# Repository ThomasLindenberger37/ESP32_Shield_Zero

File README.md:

# ESPhome Shield Zero

This project is a compact ESPhome compatible multisensor shield. The PCB is designed so that all required components can be hand-soldered—no SMD reflow oven or pick-and-place machine is required.
We want to eather use SMD componets that can be solderd by hand with a soldering iron or we want to use modules where the SMD sensors are presolderd. This makes it cheap but easy customizable.

The shield is modular and prepared for multiple purposes. The primary use case is as an ESPHome sensor with multiple sensor values available.

## Features

- Detecting human presence with LD2410B mmWave sensor
- Detecting motion with PIR sensor SR602
- Measuring brightness with PT19-21C
- 2x Onboard WS2812B LEDs for addressable color light
- SolidState Relais TLP175A for potential free contact
- Solder connections for several sensor modules like
  - BME280 -> temperature, humidity and air pressure
  - SCD40 -> CO₂, temperature and humidity
  - SHT40 -> temperature and humidity
  - and many others
- QWIIC connector for connecting additional QWIIC-compatible modules if needed

The idea is to have one general-purpose PCB and only populate the components necessary for your use case.

For example, if you want to use a SCD40 sensor to measure the CO2 level in a room, you don't a SHT40 sensor since the SCD40 already provides temperature and humidity data.

## Images

## KiBOT Export

This project uses KiBOT to automatically generate fabrication files and assets from the KiCAD project.

### Installation

KiBOT is containerized using Docker for easy installation and reproducibility. Make sure you have Docker installed on your system.

### Usage

#### Production Files (Gerber Data)

To generate the fabrication files including Gerber data, drill files, and bill of materials:

```bash
docker run --rm \
    -v "$(pwd):/home/kicad/project" \
    -u $(id -u):$(id -g) \
    -w /home/kicad/project \
    --env "HOME=/tmp" \
    ghcr.io/inti-cmnb/kicad9_auto_full:latest \
    kibot -c config.kibot.yaml
```

This command uses the `config.kibot.yaml` configuration file to generate production-ready files for PCB manufacturing, including Gerber files, drill data, and component placement information.

#### Assets (Images for Documentation)

To generate the images used in this README (schematics, 3D board views, etc.):

```bash
docker run --rm \
    -v "$(pwd):/home/kicad/project" \
    -u $(id -u):$(id -g) \
    -w /home/kicad/project \
    --env "HOME=/tmp" \
    ghcr.io/inti-cmnb/kicad9_auto_full:latest \
    kibot -c kibot_assets.kibot.yaml
```

This command uses the `kibot_assets.kibot.yaml` configuration file to generate documentation images and assets.

### Configuration Files

- **config.kibot.yaml** - Configuration for production manufacturing files (Gerber, drill files, BoM, etc.)
- **kibot_assets.kibot.yaml** - Configuration for generating documentation images and assets

### Workflow

#### Assets Generation (Pre-Commit Hook)

The asset generation should be performed before each commit to ensure that documentation images in the README are always up-to-date with the latest design changes. This is best implemented as a pre-commit hook:

1. The pre-commit hook automatically runs the asset generation command before each commit
2. If the KiCAD project has been modified, new images are generated
3. These updated assets are included in the commit

This ensures that the schematic and board images in the documentation always reflect the current PCB design.

#### Production Files (CI/CD Pipeline)

Production manufacturing files are generated automatically through a GitHub Actions pipeline whenever changes are pushed to the repository:

- The pipeline runs the `config.kibot.yaml` configuration
- Gerber files, drill data, and other manufacturing files are generated
- These files are available as build artifacts for download from the Actions tab

This automated approach ensures that fabrication files are always available and generated consistently.

Notes:
- Gerber files available from the Actions.

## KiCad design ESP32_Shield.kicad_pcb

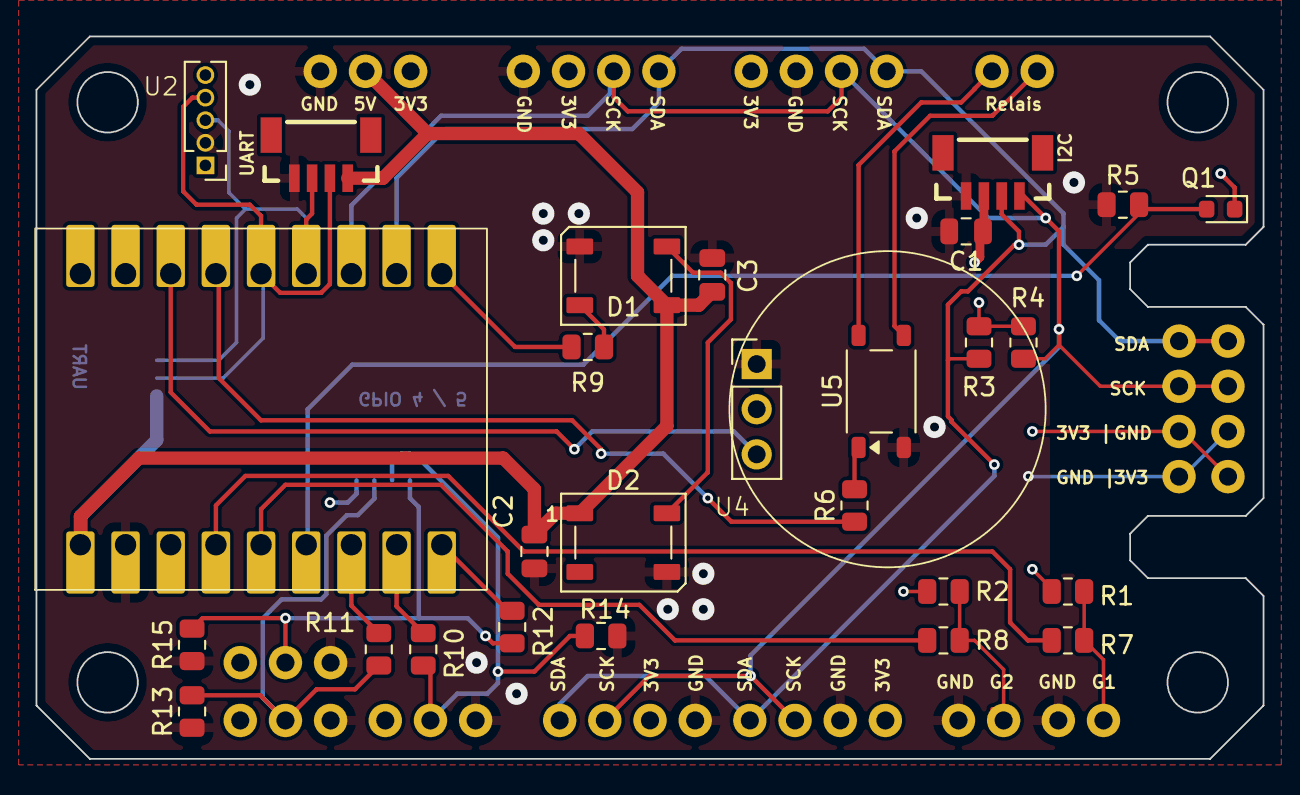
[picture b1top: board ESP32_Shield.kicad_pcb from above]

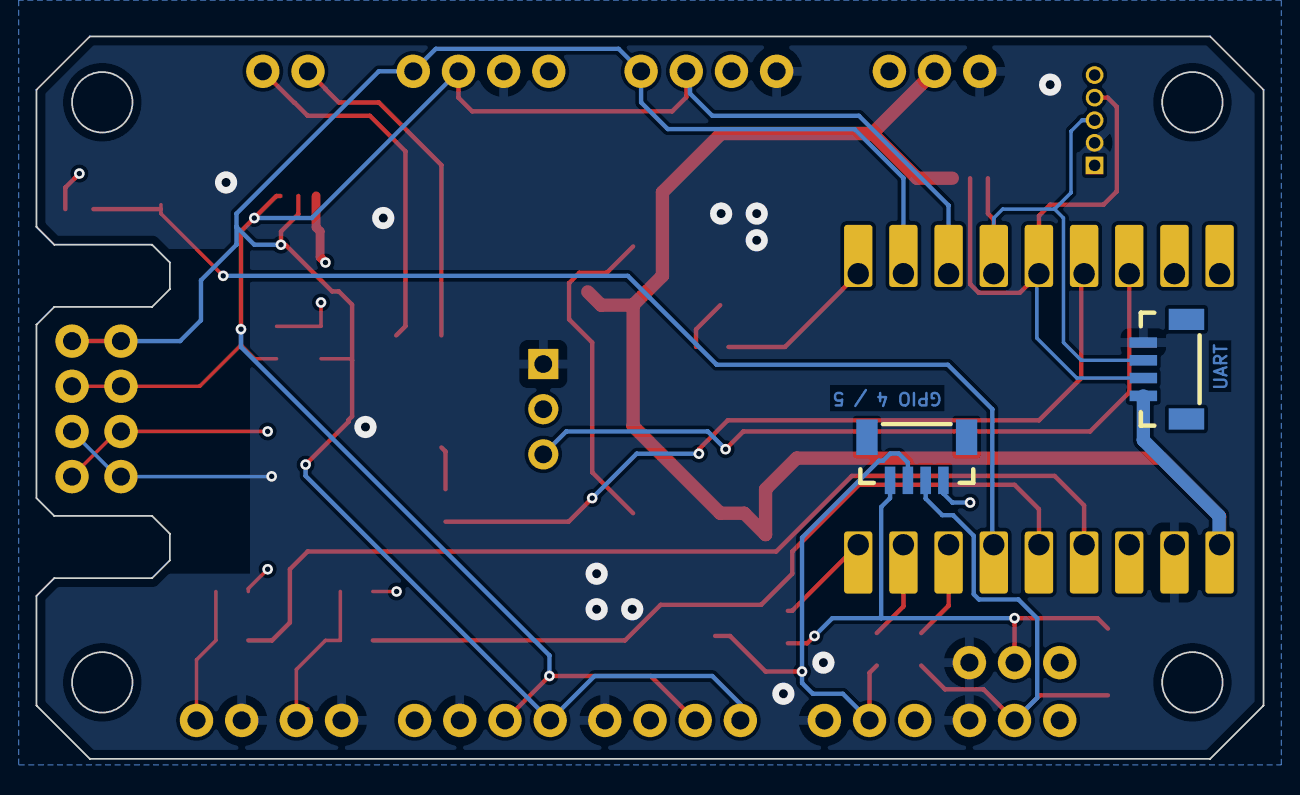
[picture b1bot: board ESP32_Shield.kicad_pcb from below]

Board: 4 copper layers, 69.0 x 40.6 mm, 42 parts (2 on the bottom side), 26 nets.

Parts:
C1: 100n; C_0805_2012Metric
C2, C3: 10u; C_0805_2012Metric
D1, D2: WS2812B; LED_WS2812B_PLCC4_5.0x5.0mm_P3.2mm
J1, J14: BME280, SHT40 Module; 1x04_P2.54mm
J2, J10, J13: SCD40 Module; 1x04_P2.54mm
J3, J5, J6: Conn_01x02; 1x02_P2.54mm
J4: Qwiic_Vertical; JST_1x04_P1.0mm_Vertical_SMD
J7, J8, J11, J12: Conn_01x03; 1x03_P2.54mm
J9: VL53L0X Module; 1x04_P2.54mm
J15, J16, J17: mmWave Connector; JST_1x04_P1.0mm_Vertical_SMD
Q1: PT19-21C; LED_0603_1608Metric
R1, R2: 4k7; R_0805_2012Metric
R3, R4, R9, R13, R14, R15: 2k2; R_0805_2012Metric
R5: 10k; R_0805_2012Metric
R6, R7, R8, R10, R11, R12: 470R; R_0805_2012Metric
U1: ESP32_S3_zeroBoard
U2: Unbenannt
U4: PIR_SR602
U5: TLP175A; Toshiba_SOIC-4-6_4.4x3.6mm_P1.27mm

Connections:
+3V3: C1.1, J1.1, J2.2, J4.2, J7.3, J8.3, J9.1, J10.2, J11.3, J12.3, J13.2, J14.1, J17.4, Q1.1 (C), R1.2, R2.2, R3.2, R4.2, U1.3 (3V3), U2.1 (VCC), U4.2 (VCC)
+5V: C2.1, C3.1, D1.1 (VDD), D2.1 (VDD), J11.2, J15.4, J16.4, U1.1 (5V)
GND: C1.2, C2.2, C3.2, D1.3 (VSS), D2.3 (VSS), J1.2, J2.1, J4.1, J5.1, J6.1, J7.1, J8.1, J9.2, J10.1, J11.1, J12.1, J13.1, J14.2, J15.1, J16.1, R5.1, R13.1, R14.1, R15.1, U1.2 (GND), U2.2 (GND), U4.1 (GND), U5.3
GPIO_1: R7.2, U1.4 (GP1)
GPIO_2: R8.2, U1.5 (GP2)
GPIO_4: R11.2, U1.7 (GP4)
GPIO_4_: J7.2, J17.3, R11.1, R13.2
GPIO_5: R10.2, U1.8 (GP5)
GPIO_5_: J8.2, J17.2, R10.1, R14.2
GPIO_6: R12.2, U1.9 (GP6)
GPIO_6_: J12.2, J17.1, R12.1, R15.2
unnamed: D1.4 (DIN), R9.2
unnamed: D1.2 (DOUT), D2.4 (DIN)
unnamed: J3.1, U5.6
unnamed: J3.2, U5.4
unnamed: J5.2, R2.1, R8.1
unnamed: J6.2, R1.1, R7.1
unnamed: R6.2, U5.1
PIR: U1.16 (GP13), U4.3 (SIGN)
PhotoMeas: Q1.2 (E), R5.2, U1.6 (GP3)
Relais: R6.1, U1.15 (GP12)
SCK: J1.3, J2.3, J4.4, J9.3, J10.3, J13.3, J14.3, R4.1, U1.12 (GP9)
SDA: J1.4, J2.4, J4.3, J9.4, J10.4, J13.4, J14.4, R3.1, U1.11 (GP8)
UART_RX_mmWAVE: J15.2, J16.2, U1.13 (GP10), U2.3 (RX)
UART_TX_mmWAVE: J15.3, J16.3, U1.14 (GP11), U2.4 (TX)
WS12_LED_IN: R9.1, U1.10 (GP7)

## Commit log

2026-02-04 tweek the pipeline
2026-02-05 suppress warnig for missing 3D models
2026-02-05 fix kibot file to eable gerber generation
2026-02-06 remove xml from gitignore
2026-02-07 working kibotfile for gerber
2026-02-08 separate assets generation form prodution files
2026-02-08 blender export is doing someting
2026-02-08 removed xml form git
2026-02-08 Assets generation works
2026-02-08 minor changes on brd
2026-02-08 fix readme
2026-02-08 udpate readme
2026-02-08 ready for order
2026-02-08 fix naing shield
2026-02-08 add github action for generating the gerber
2026-02-08 Allow CI to run on 'develop' branch
2026-02-08 imporve readme
2026-02-08 update workflow file
2026-02-08 try other docker image
2026-02-08 try other docker image again
2026-02-08 add status badge to readme
2026-02-20 remove fix soldered tempertaure sesor
2026-02-21 enhance README with KiBOT usage instructions and asset generation workflow
2026-02-21 make shure everithing is english
2026-02-21 improve readme
2026-02-21 fix upload path
2026-02-21 fix tittle in readme
2026-02-21 add silk screen and mmWave connector
2026-02-21 Update artifact name in fabrication workflow
2026-02-22 try other pr pipeline
2026-02-22 add more JST connectors for UART
2026-02-22 add jst connector for aditional gpios
2026-02-22 Feature/description on soldermask (#2)
    * fix Readme
    * enhance README with KiBOT usage instructions and asset generation workflow
    * make shure everithing is english
    * improve readme
    * fix upload path
    * fix tittle in readme
2026-02-22 Feature/merge develop to main (#3)
    * remove fix soldered tempertaure sesor
    * Feature/description on soldermask (#2)
    * fix Readme
    * enhance README with KiBOT usage instructions and asset generation workflow
    * make shure everithing is english
    * improve readme
